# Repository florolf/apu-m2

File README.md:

# apu-m2

This repo contains the hardware design for an adapter/holder combination that allows installing a 2280 M.2 NVMe SSD into a [PC Engines APU2](https://pcengines.ch/apu2.htm) board.

(This picture shows an older version of the design with some bodges applied, the version released here should just work out of the box, see [below](#revision-notes))

## Why?

The original apu2 board only allows SD cards/mSATA SSDs for storage. The former is not very performant/durable and the latter is getting rarer/more expensive per GB. There's also a regular SATA connector, but regular SATA SSDs don't fit well into the standard enclosure.

Conversely, M.2 SSDs are a staple piece of hardware nowadays. PCIe/NVMe is also a nicer interface compared to SATA (although raw throughput is approximately the same here, since we are trading SATA 3.0 for 1× PCIe Gen 2).

## Why not?

There's a number of downsides:

 - You lose 1 mPCIe slot (for the M.2 adapter) _and_ the mSATA slot (for the holder PCB)
 - You likely also lose the second mPCIe slot (which the M.2 card bridges over) depending on the height of the card you want to place in that slot
 - Cooling can be a concern (see [below](#cooling))

## Ordering

The adapter PCB is designed for the 4-layer [JLCPCB](https://jlcpcb.com) "JLC7628" stackup, with 1mm thickness:

The holder PCB is mainly mechanical, so there are no special requirements other than 1mm thickness.

The respective `fab/` directories contain the Gerber files that can be submitted to JLCPCB.

### Revision notes

Version 1.0 of the adapter PCB had the RX/TX lanes swapped because the mPCIe spec and the M.2 spec use different perspectives for describing the data transfer direction. Version 1.1, published here, fixes this and also adds some more assembly options for handshaking signals and additional decoupling. None of those are strictly necessary though, so the `DNP` annotations in the schematic reflect the electrical behavior of v1.0 (except for the RX/TX crossover), which has been working well in practice.

### BOM

For a minimal configuration, you only need:

 - 1× JAE SM3ZS067U410AMR1000 M.2 socket ([Digikey link](https://www.digikey.de/en/products/detail/jae-electronics/SM3ZS067U410AMR1000/4162231))
 - A mounting screw (I've used [these](https://www.amazon.de/gp/product/B087C1G4ZF), but "ASUS / ASROCK short M.2 screw" seems to be a good keyword in general)
 - 3× 0402 0 Ohm resistors (or just use a solder bridge)

## Software requirements

If you want to use the NVMe SSD as a boot drive, you'll need a recent version of the [APU coreboot firmware](https://pcengines.github.io/) (containing SeaBIOS 1.16.0 or newer), since a number of NVMe-related issues were only fixed recently.

## Cooling

At least in my experiments, the M.2 SSD got relatively hot (although I didn't compare this with the original mSATA SSD, so this could just be normal).

Internal monitoring (via `nvme smart-log`) showed temperatures exceeding 60 °C at an ambient air temperature of about 20 °C. This was a little too much for my taste, so I added a [Würth WE-TGFG](https://www.we-online.com/catalog/en/THERMAL_WE-TGFG) gasket (order number 407150015115) to bond the NVMe to the APU enclosure. With this, the temperature never exceeds 50 °C.

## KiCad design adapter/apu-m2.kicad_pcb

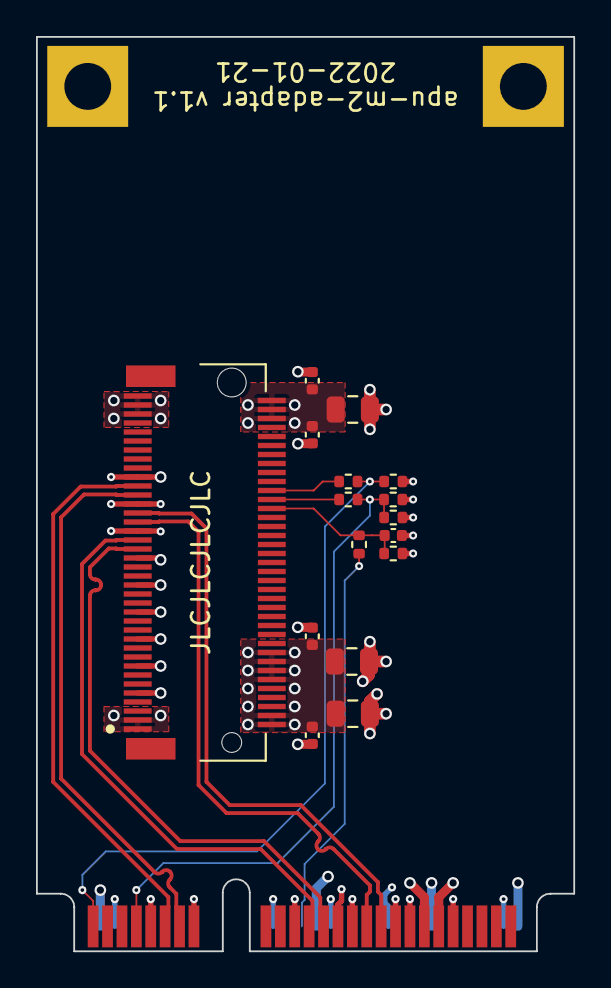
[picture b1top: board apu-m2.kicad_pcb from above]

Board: 4 copper layers, 29.8 x 50.8 mm, 17 parts (0 on the bottom side), 14 nets.

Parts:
C1: C_Small; C_0402_1005Metric
C2, C3, C4: 10u; C_0805_2012Metric
C5, C6, C7, C8: 100n; C_0402_1005Metric
J1: Bus_PCI_Express_Mini; mPCIe_Edge
J2: Bus_M.2_Socket_M; JAE_SM3ZS067UxxM
R1, R2, R3: 10k; R_0402_1005Metric
R4, R5, R6, R7: 0R; R_0402_1005Metric

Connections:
+3V3: C2.1, C3.1, C4.1, C5.1, C6.1, C7.1, C8.1, J1.2 (+3V3AUX), J1.24 (+3V3AUX), J1.39 (+3V3AUX), J1.41 (+3V3AUX), J1.52 (+3V3AUX), J2.2 (3.3V), J2.4 (3.3V), J2.12 (3.3V), J2.14 (3.3V), J2.16 (3.3V), J2.18 (3.3V), J2.70 (3.3V), J2.72 (3.3V), J2.74 (3.3V), R1.1, R2.1, R3.1
/PER0+: J1.25 (PERp0), J2.41 (PERn0/SATA-B+)
/PER0-: J1.23 (PERn0), J2.43 (PERp0/SATA-B-)
/PET0+: J1.33 (PETp0), J2.49 (PETp0/SATA-A+)
/PET0-: J1.31 (PETn0), J2.47 (PETn0/SATA-A-)
/REFCLK+: J1.13 (REFCLK+), J2.53 (REFCLKn)
/REFCLK-: J1.11 (REFCLK-), J2.55 (REFCLKp)
/~CLKREQ: J1.7 (~CLKREQ), R2.2, R5.2, R6.1
/~PERST: C1.1, J2.50 (~PERST), R1.2, R4.1
/~PEWAKE: J1.1 (~WAKE), R3.2, R7.1
GND: C1.2, C2.2, C3.2, C4.2, C5.2, C6.2, C7.2, C8.2, J1.4 (GND), J1.9 (GND), J1.15 (GND), J1.18 (GND), J1.21 (GND), J1.26 (GND), J1.27 (GND), J1.29 (GND), J1.34 (GND), J1.35 (GND), J1.37 (GND), J1.40 (GND), J1.43 (GND), J1.50 (GND), J2.1 (GND), J2.3 (GND), J2.9 (GND), J2.15 (GND), J2.21 (GND), J2.27 (GND), J2.33 (GND), J2.39 (GND), J2.45 (GND), J2.51 (GND), J2.57 (GND), J2.71 (GND), J2.73 (GND), J2.75 (GND), R5.1
unnamed: J1.22 (~PERST), R4.2
unnamed: J2.52 (~CLKREQ), R6.2
unnamed: J2.54 (~PEWAKE), R7.2

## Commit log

2022-06-12 import
